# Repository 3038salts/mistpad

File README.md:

# mistpad

mistpad is a 4-key macropad featuring an OLED Display and 4 SK6812 mini-LEDs. It uses QMK firmware.

## CAD Model:

Made with Autodesk Fusion

## Schematic

## PCB

Made with KiCAD

## BOM:
- 1x Seeed XIAO RP2040
- 4x Cherry MX Switches
- 4x DSA Keycaps
- 1x 0.91" 128x32 OLED Display
- 4x M3x5x4 Heatset inserts
- 4x M3x16mm screws
- 4x SK6812 LEDs
- 1x Case (2 3D-printed parts)

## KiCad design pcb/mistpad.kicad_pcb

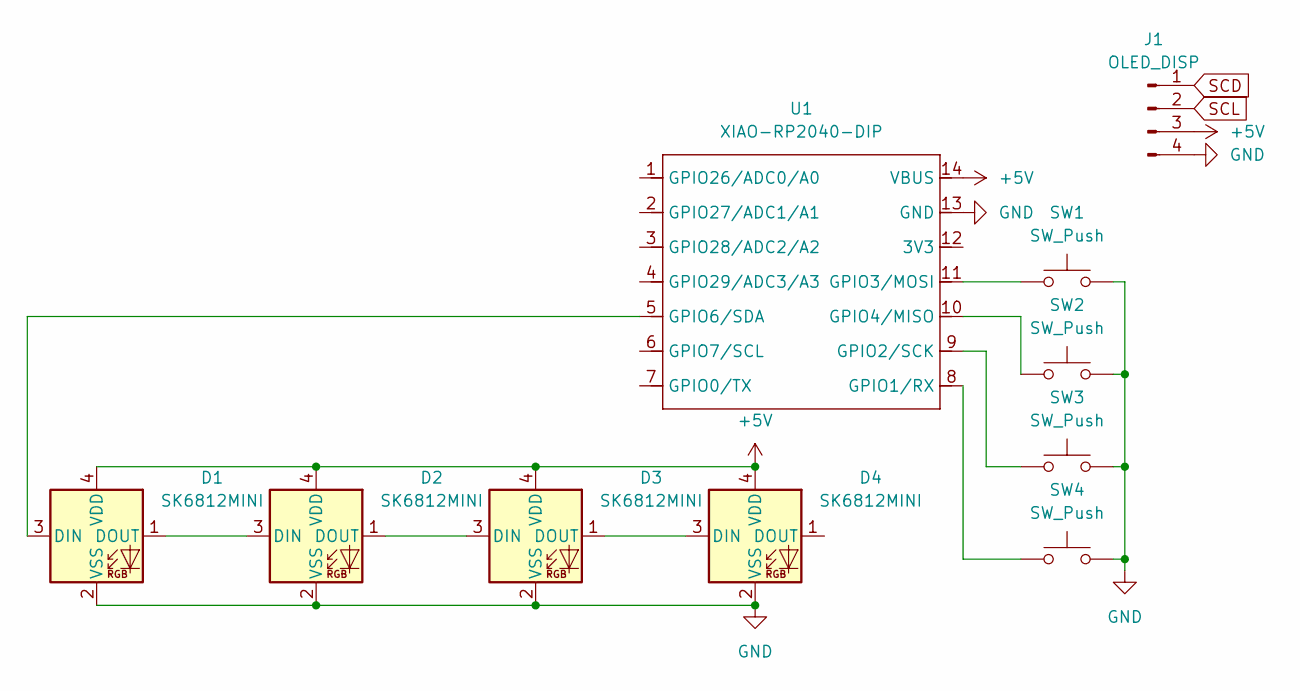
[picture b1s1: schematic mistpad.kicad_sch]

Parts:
D1, D2, D3, D4: SK6812MINI; LED_SK6812MINI_PLCC4_3.5x3.5mm_P1.75mm
J1: OLED_DISP; SSD1306-0.91-OLED-4pin-128x32
SW1, SW2, SW3, SW4: SW_Push; SW_Cherry_MX_1.00u_PCB
U1: XIAO-RP2040-DIP

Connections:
+5V: D1.4 (VDD), D2.4 (VDD), D3.4 (VDD), D4.4 (VDD), J1.3, U1.14 (VBUS)
GND: D1.2 (VSS), D2.2 (VSS), D3.2 (VSS), D4.2 (VSS), J1.4, SW1.2, SW2.2, SW3.2, SW4.2, U1.13 (GND)
unnamed: D1.3 (DIN), U1.5 (GPIO6/SDA)
unnamed: D1.1 (DOUT), D2.3 (DIN)
unnamed: D2.1 (DOUT), D3.3 (DIN)
unnamed: D3.1 (DOUT), D4.3 (DIN)
unnamed: SW4.1, U1.8 (GPIO1/RX)
unnamed: SW3.1, U1.9 (GPIO2/SCK)
unnamed: SW1.1, U1.11 (GPIO3/MOSI)
unnamed: SW2.1, U1.10 (GPIO4/MISO)
SCD: J1.1
SCL: J1.2

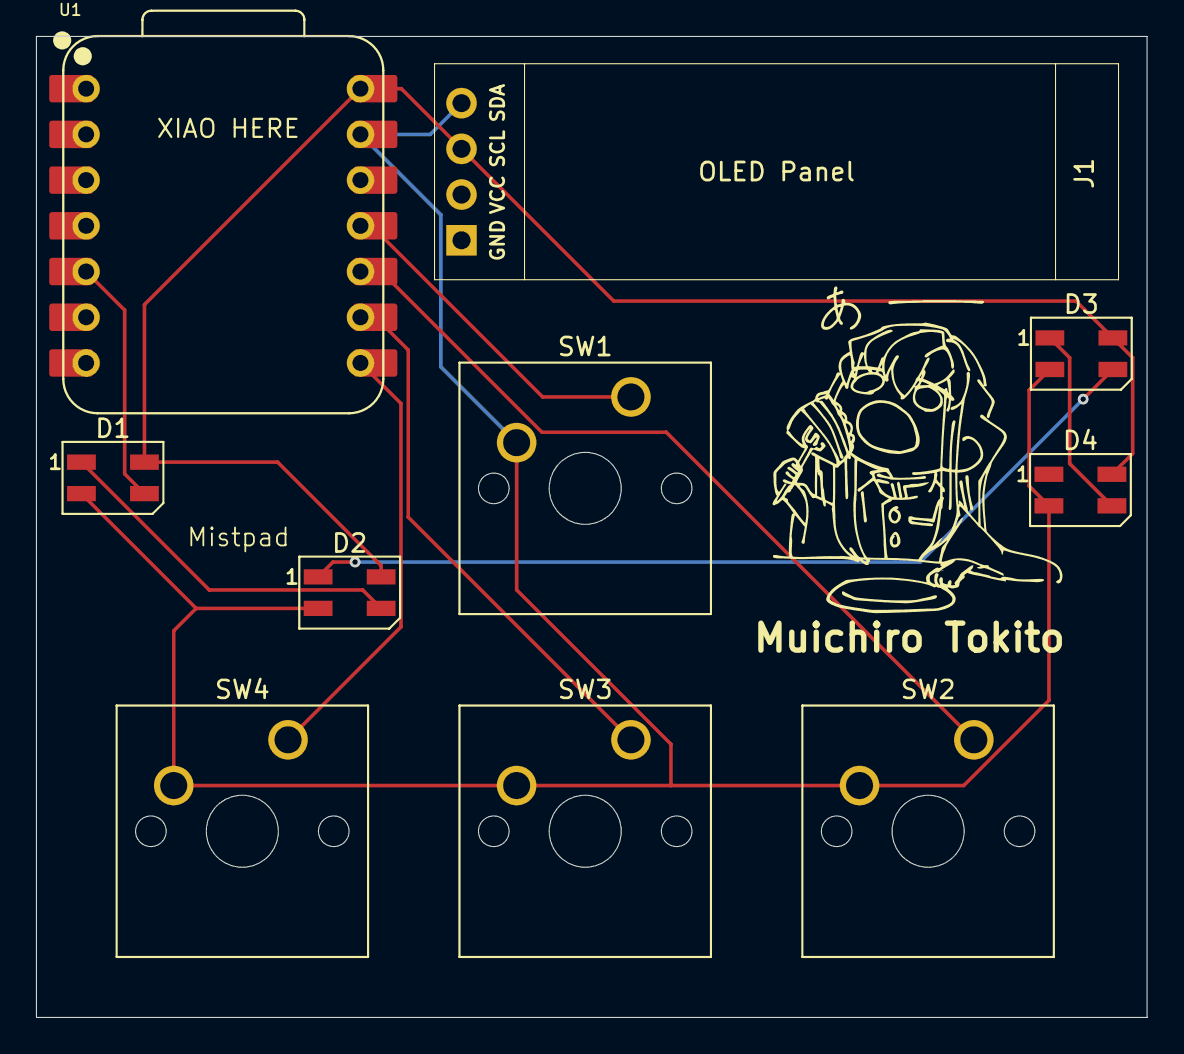
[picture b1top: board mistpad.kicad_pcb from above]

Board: 2 copper layers, 61.7 x 54.5 mm, 11 parts (0 on the bottom side), 10 nets.

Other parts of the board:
Muichiro Tokito: LOGO; design

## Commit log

2026-01-05 Added all files
2026-01-06 Separated case files
2026-01-06 Modified PCB (display orientation)
2026-01-06 Fixed case design and updated screenshots
2026-01-06 Fixed README
2026-01-06 Made images bigger
